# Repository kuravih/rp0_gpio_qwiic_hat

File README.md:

# Raspberry Pi qwiic hat

Raspberry pi GPIO pins can can be configured as i<sup>2</sup>c as described [here][1].
There are 28 GPIO pins which can be configured as 14 i<sup>2</sup>c buses in total.
This hat wires these 14 i<sup>2</sup>c busses including the [5 V rail][3] and the ground to 14 [qwiic][2] connectors.
Add the following to the `[all]` section of the `/boot/firmware/config.txt` file to enable the i<sup>2</sup>c busses.
The i<sup>2</sup>c devices will be available at `dev/i2c-n` (where n will be the bus number used in the dtoverlay).
This setup along with ~100 [ds28ea00_sensorlets][4] were flown on PICTURE-C flight in 2025 to continuously monitor the instrument temperature at numerous locations.

    dtoverlay=i2c-gpio,i2c_gpio_sda=27,i2c_gpio_scl=18,bus=10
    dtoverlay=i2c-gpio,i2c_gpio_sda=25,i2c_gpio_scl=9,bus=11
    dtoverlay=i2c-gpio,i2c_gpio_sda=5,i2c_gpio_scl=11,bus=12
    dtoverlay=i2c-gpio,i2c_gpio_sda=12,i2c_gpio_scl=6,bus=13
    dtoverlay=i2c-gpio,i2c_gpio_sda=19,i2c_gpio_scl=26,bus=14
    dtoverlay=i2c-gpio,i2c_gpio_sda=15,i2c_gpio_scl=17,bus=15
    dtoverlay=i2c-gpio,i2c_gpio_sda=23,i2c_gpio_scl=22,bus=16
    dtoverlay=i2c-gpio,i2c_gpio_sda=10,i2c_gpio_scl=24,bus=17
    dtoverlay=i2c-gpio,i2c_gpio_sda=1,i2c_gpio_scl=0,bus=18
    dtoverlay=i2c-gpio,i2c_gpio_sda=2,i2c_gpio_scl=3,bus=19
    dtoverlay=i2c-gpio,i2c_gpio_sda=4,i2c_gpio_scl=14,bus=20
    dtoverlay=i2c-gpio,i2c_gpio_sda=7,i2c_gpio_scl=8,bus=21
    dtoverlay=i2c-gpio,i2c_gpio_sda=20,i2c_gpio_scl=21,bus=22
    dtoverlay=i2c-gpio,i2c_gpio_sda=16,i2c_gpio_scl=13,bus=23

## Schematic

## PCB

## Photos

[1]: https://forums.raspberrypi.com/viewtopic.php?t=205576
[2]: https://www.sparkfun.com/qwiic
[3]: https://pinout.xyz/pinout/5v_power 
[4]: https://github.com/kuravih/ds28ea00_sensorlet

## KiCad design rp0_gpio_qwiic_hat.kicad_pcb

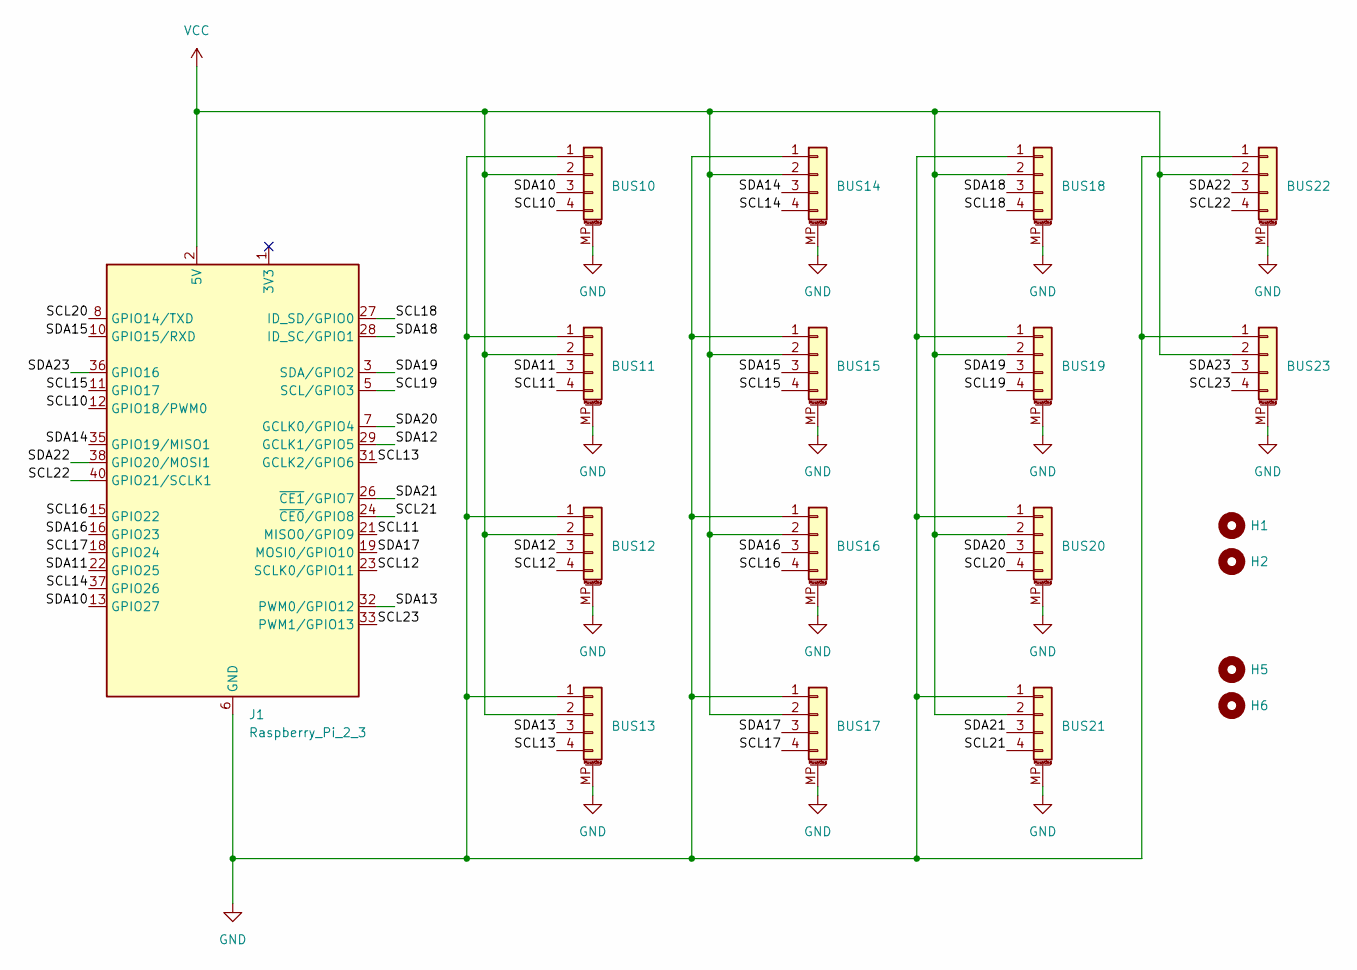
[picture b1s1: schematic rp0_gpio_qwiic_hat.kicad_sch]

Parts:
BUS10, BUS11, BUS12, BUS13, BUS14, BUS15, BUS16, BUS17, BUS18, BUS19, BUS20, BUS21, BUS22, BUS23: Conn_01x04_MountingPin; JST_SH_BM04B-SRSS-TB_1x04-1MP_P1.00mm_Vertical; JLCPCB Part # C160390
H1, H2, H5, H6: MountingHole; MountingHole_2.7mm_M2.5
J1: Raspberry_Pi_2_3; PinSocket_2x20_P2.54mm_Vertical_SMD; JLCPCB Part # C3975165

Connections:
/SCL10: BUS10.4, J1.12 (GPIO18/PWM0)
/SCL11: BUS11.4, J1.21 (MISO0/GPIO9)
/SCL12: BUS12.4, J1.23 (SCLK0/GPIO11)
/SCL13: BUS13.4, J1.31 (GCLK2/GPIO6)
/SCL14: BUS14.4, J1.37 (GPIO26)
/SCL15: BUS15.4, J1.11 (GPIO17)
/SCL16: BUS16.4, J1.15 (GPIO22)
/SCL17: BUS17.4, J1.18 (GPIO24)
/SCL18: BUS18.4, J1.27 (ID_SD/GPIO0)
/SCL19: BUS19.4, J1.5 (SCL/GPIO3)
/SCL20: BUS20.4, J1.8 (GPIO14/TXD)
/SCL21: BUS21.4, J1.24 (~CE0/GPIO8)
/SCL22: BUS22.4, J1.40 (GPIO21/SCLK1)
/SCL23: BUS23.4, J1.33 (PWM1/GPIO13)
/SDA10: BUS10.3, J1.13 (GPIO27)
/SDA11: BUS11.3, J1.22 (GPIO25)
/SDA12: BUS12.3, J1.29 (GCLK1/GPIO5)
/SDA13: BUS13.3, J1.32 (PWM0/GPIO12)
/SDA14: BUS14.3, J1.35 (GPIO19/MISO1)
/SDA15: BUS15.3, J1.10 (GPIO15/RXD)
/SDA16: BUS16.3, J1.16 (GPIO23)
/SDA17: BUS17.3, J1.19 (MOSI0/GPIO10)
/SDA18: BUS18.3, J1.28 (ID_SC/GPIO1)
/SDA19: BUS19.3, J1.3 (SDA/GPIO2)
/SDA20: BUS20.3, J1.7 (GCLK0/GPIO4)
/SDA21: BUS21.3, J1.26 (~CE1/GPIO7)
/SDA22: BUS22.3, J1.38 (GPIO20/MOSI1)
/SDA23: BUS23.3, J1.36 (GPIO16)
GND: BUS10.1, BUS10.MP (MountPin), BUS11.1, BUS11.MP (MountPin), BUS12.1, BUS12.MP (MountPin), BUS13.1, BUS13.MP (MountPin), BUS14.1, BUS14.MP (MountPin), BUS15.1, BUS15.MP (MountPin), BUS16.1, BUS16.MP (MountPin), BUS17.1, BUS17.MP (MountPin), BUS18.1, BUS18.MP (MountPin), BUS19.1, BUS19.MP (MountPin), BUS20.1, BUS20.MP (MountPin), BUS21.1, BUS21.MP (MountPin), BUS22.1, BUS22.MP (MountPin), BUS23.1, BUS23.MP (MountPin), J1.6 (GND), J1.9 (GND), J1.14 (GND), J1.20 (GND), J1.25 (GND), J1.30 (GND), J1.34 (GND), J1.39 (GND)
VCC: BUS10.2, BUS11.2, BUS12.2, BUS13.2, BUS14.2, BUS15.2, BUS16.2, BUS17.2, BUS18.2, BUS19.2, BUS20.2, BUS21.2, BUS22.2, BUS23.2, J1.2 (5V), J1.4 (5V)

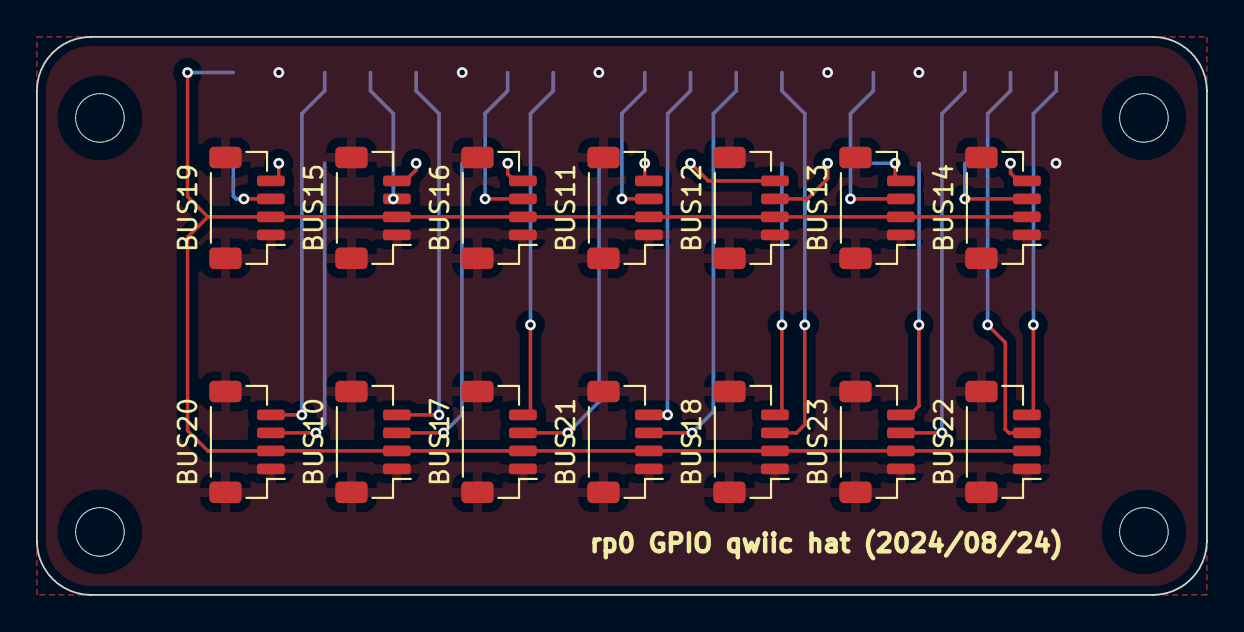
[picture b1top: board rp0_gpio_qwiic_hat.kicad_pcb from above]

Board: 2 copper layers, 65.0 x 31.0 mm, 19 parts (1 on the bottom side), 30 nets.

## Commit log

2026-03-01 Add files
2026-03-03 Readme edits
